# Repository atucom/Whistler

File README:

Whistler:

What is it?
  A small handheld device that precisely mimics the tone and volume of a HID RFID card readers
Why?
  Often times on Red Team engagements, you will gain access to a building via tailgating. Sometimes, if the employees are well trained, they will turn around and ask you to make sure you badge in if they don't see the movement and/or hear the characteristic beep of a card read.
Design?
  The design of the latest version is a very simplistic circuit. I use an RC circuit to control the timing of a 555 timer which controls an NPN transistor hooked up to a Star Micronics TMB-05. The RC circuit controls the discharge of the capacitor for a precise amount of time. I'v measured the beep time on a number of readers and they all seem to be ~250ms. I've replicated the beep time fairly precisely as seen on my oscilloscope.

Bill of Materials:
  For Revision E
    1x 2.2 Mega Ohm Resistor
    1x 1.0 Kilo Ohm Resistor
    2x 0.1uF Capacitor
    1x TMB-05
    1x 555 Timer
    2x CR1220 Coin Cell Batteries

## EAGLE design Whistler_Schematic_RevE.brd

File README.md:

# Whistler
### What is it?
A small handheld device that precisely mimics the tone and volume of a HID RFID card readers
### Why?
Often times on Red Team engagements, you will gain access to a building via tailgating. Sometimes, if the employees are well trained, they will turn around and ask you to make sure you badge in if they don't see the movement and/or hear the characteristic beep of a card read.
### Design
The design of the latest version is a very simplistic circuit. I use an RC circuit to control the timing of a 555 timer which controls an NPN transistor hooked up to a Star Micronics TMB-05. The RC circuit controls the discharge of the capacitor for a precise amount of time. I'v measured the beep time on a number of readers and they all seem to be ~250ms. I've replicated the beep time fairly precisely as seen on my oscilloscope:

### Bill of Materials:
For Revision E:
* 1x 2.2 Mega Ohm Resistor
* 1x 1.0 Kilo Ohm Resistor
* 2x 0.1uF Capacitor
* 1x TMB-05
* 1x 555 Timer
* 2x CR1220 Coin Cell Batteries
* 1x Pushbutton
* 2x CR1220 Coin Cell Holders
* 1x NPN Transistor

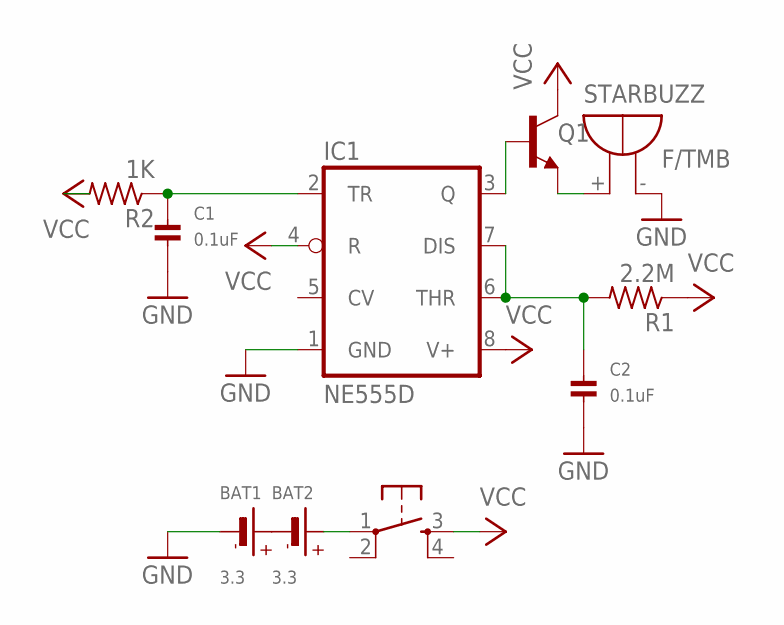
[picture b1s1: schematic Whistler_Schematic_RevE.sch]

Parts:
BAT1, BAT2: 3.3; CR1220
C1, C2: 0.1uF; _0805
IC1: NE555D; SO08
Q1: TRANS_NPN-MMBT2222AL; SOT23-3
R1: 2.2M; R1206
R2: 1K; R1206
S2: TAC_SWITCHSMD; TACTILE-SWITCH-SMD
STARBUZZ: F/TMB

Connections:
GND: BAT1.-, C1.2, C2.2, IC1.1 (GND), STARBUZZ.-
unnamed: C2.1, IC1.6 (THR), IC1.7 (DIS), R1.2
unnamed: C1.1, IC1.2 (TR), R2.1
unnamed: BAT1.+$1 (+), BAT2.-
unnamed: IC1.3 (Q), Q1.1 (B)
unnamed: BAT2.+$1 (+), S2.1
unnamed: Q1.2 (E), STARBUZZ.+
VCC: IC1.4 (R), IC1.8 (V+), Q1.3 (C), R1.1, R2.2, S2.3

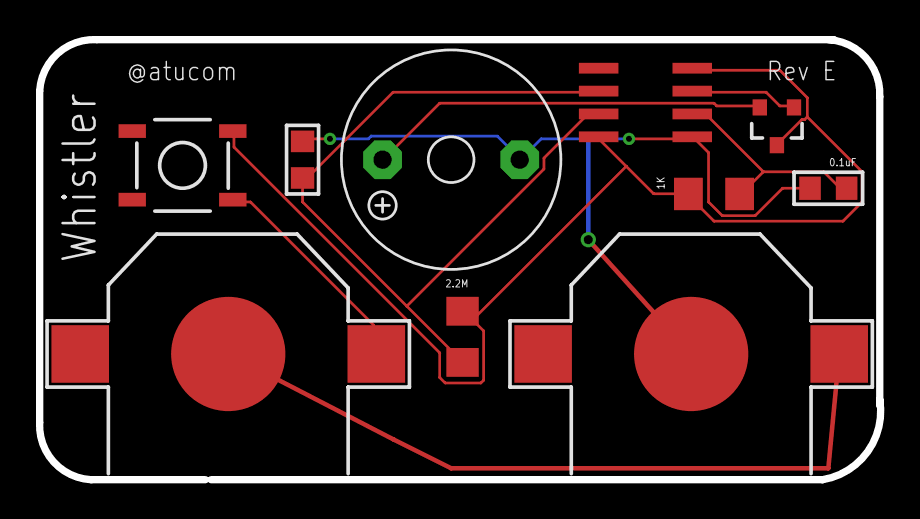
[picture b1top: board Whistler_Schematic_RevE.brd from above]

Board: 2 copper layers, 46.7 x 24.4 mm, 10 parts (0 on the bottom side), 8 nets.

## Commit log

2017-03-23 adding initial files

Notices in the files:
parts and their libraries:
microbuilder: This work is placed in the public domain, and may be freely used for commercial and non-commercial work with the following conditions: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
SparkFun-Retired: Licensing: Creative Commons ShareAlike 4.0 International - https://creativecommons.org/licenses/by-sa/4.0
